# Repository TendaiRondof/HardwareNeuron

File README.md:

# HardwareNeuron
Eine Brufsmaturitätsarbeit für die BBW Winterthur.

## Abstract
### Deutsch
In dieser BMA stellen wir, Tendai und Malik, uns die Frage, ob es möglich ist, mit simplen elektronischen Bauteilen eine Schaltung zu entwerfen, die bestimmte, elementare Logik erlernen und anschliessend wiedergeben kann. Um dies zu erreichen, verwenden wir das Modell eines Neurons. Wir erläutern Struktur und Funktion des biologischen und des informatischen Modells. Schliesslich fällt unsere, ausführlich begründete Entscheidung auf das spiking neural Network. Das die Version des informatischen Modells, welches dem bioligischen am nächsten kommt. Danach nähern wir uns mittels mathematischen Formeln, basierend auf dem spiking neural Network, den Funktionen an, welche die Schaltung erfüllen muss. Darauffolgend werden die Teilfunktionen erklärt und es wird erläutert, wie unsere Schaltung sie bewältigen soll. Die Messungen des Prototypen zeigen, dass die Vorwärtsrechnung, also das wiedergeben des gelernten, funktioniert. Das Problem ist, dass bei unserem Endprodukt nichts funktioniert, da die Leiterbahnen auf dieser Version sehr kurzschlussanfällig sind und wir keine Zeit mehr hatten, alle Kurzschlüsse zu beheben.
### English
In this BMA we, that’s Malik and Tendai, ask ourselves, wether or not it’s possible, to design an electrical circuit, which can learn certain, elementary logic and replicate it subsequently. In order to reach this, we use the model of a neuron. We explain structure and function of the biological and informatical model. In the end, our decision falls onto the spiking neural network. That’s the informatical model, which comes closest to the biological one. Then, we draw up the functions, that our circuit has to implement, through mathematical formulas. After that, the purposes of the smaller subcircuits, we designed, is explained. In the measurements of the Prototype it is shown, that the replication of logic works. Unfortunately the learning itself doesn’t. Besides of that, our final product doesn’t work at all, because there are shortcircuits all over the print and we didn’t have time, to repair them all.

Von Tendai Rondof und Malik Schneider

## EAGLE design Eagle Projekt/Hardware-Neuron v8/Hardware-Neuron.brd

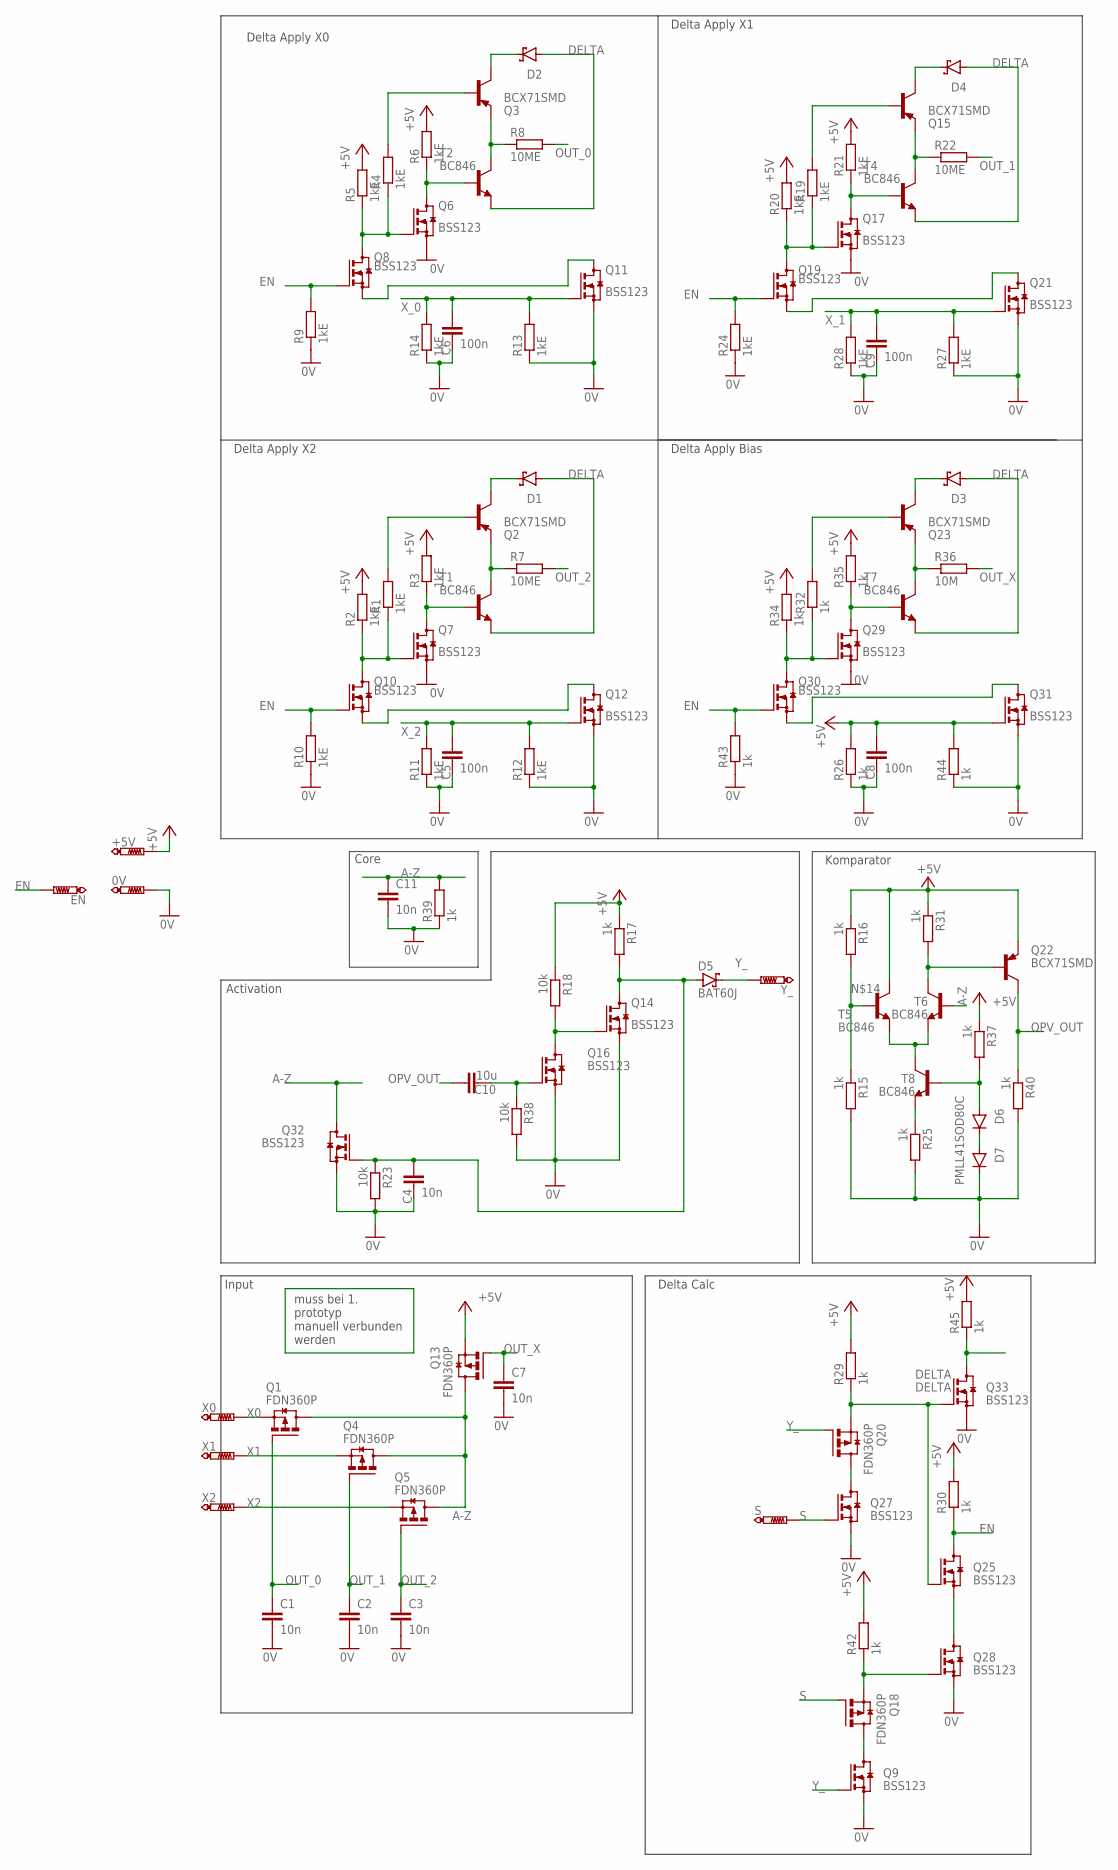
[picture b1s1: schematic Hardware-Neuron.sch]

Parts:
0V: PTR1PAD1-17; P1-17
+5V: PTR1PAD1-17; P1-17
C1, C2, C3, C4, C7, C11: 10n; C0805
C5, C6, C8, C9: 100n; C0805
C10: 10u; C0805
D1, D2, D3, D4, D5: BAT60J; SOD323_ST
D6, D7: PMLL41SOD80C; SOD80C
EN: PTR1PAD1-17; P1-17
Q1, Q4, Q5, Q13, Q18, Q20: FDN360P; SUPER-SOT3
Q2, Q3, Q15, Q22, Q23: BCX71SMD; SOT23
Q6, Q7, Q8, Q9, Q10, Q11, Q12, Q14, Q16, Q17, Q19, Q21, Q25, Q27, Q28, Q29, Q30, Q31, Q32, Q33: BSS123; SOT23
R1, R2, R3, R4, R5, R6, R9, R10, R11, R12, R13, R14, R19, R20, R21, R24, R27, R28: 1kE; M0805
R7, R8, R22: 10ME; M0805
R15, R16, R17, R25, R26, R29, R30, R31, R32, R34, R35, R37, R39, R40, R42, R43, R44, R45: 1k; M0805
R18, R23, R38: 10k; M0805
R36: 10M; M0805
S: PTR1PAD1-17; P1-17
T1, T2, T4, T5, T6, T7, T8: BC846; SOT23
X0, X1, X2: PTR1PAD1-17; P1-17
Y_: PTR1PAD1-17; P1-17

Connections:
0V: 0V.TP, C1.2, C2.2, C3.2, C4.2, C5.2, C6.2, C7.2, C8.2, C9.2, C11.2, D7.C, Q6.2 (S), Q7.2 (S), Q9.2 (S), Q11.2 (S), Q12.2 (S), Q14.2 (S), Q16.2 (S), Q17.2 (S), Q21.2 (S), Q27.2 (S), Q28.2 (S), Q29.2 (S), Q31.2 (S), Q32.2 (S), Q33.2 (S), R9.1, R10.1, R11.1, R12.1, R13.1, R14.1, R15.2, R23.2, R24.1, R25.2, R26.1, R27.1, R28.1, R38.2, R39.1, R40.2, R43.1, R44.1
+5V: +5V.TP, C8.1, Q13.2 (S), Q22.2 (E), Q31.1 (G), R2.2, R3.2, R5.2, R6.2, R16.1, R17.1, R18.1, R20.2, R21.2, R26.2, R29.2, R30.2, R31.1, R34.2, R35.2, R37.1, R42.2, R44.2, R45.2, T5.3 (C)
A-Z: C11.1, Q1.3 (D), Q4.3 (D), Q5.3 (D), Q13.3 (D), Q32.3 (D), R39.2, T6.1 (B)
DELTA: D1.A, D2.A, D3.A, D4.A, Q20.2 (S), Q25.1 (G), Q33.1 (G), R29.1, T1.2 (E), T2.2 (E), T4.2 (E), T7.2 (E)
EN: EN.TP, Q8.1 (G), Q10.1 (G), Q19.1 (G), Q25.3 (D), Q30.1 (G), R9.2, R10.2, R24.2, R30.1, R43.2
unnamed: Q29.3 (D), R35.1, T7.1 (B)
unnamed: Q23.2 (E), R36.1, T7.3 (C)
unnamed: C10.2, Q16.1 (G), R38.1
unnamed: Q33.3 (D), R45.1
unnamed: Q14.1 (G), Q16.3 (D), R18.2
unnamed: Q6.3 (D), R6.1, T2.1 (B)
unnamed: Q8.2 (S), Q11.3 (D)
unnamed: Q3.2 (E), R8.1, T2.3 (C)
unnamed: D3.C, Q23.3 (C)
unnamed: Q23.1 (B), R32.2
unnamed: Q29.1 (G), Q30.3 (D), R32.1, R34.1
unnamed: Q30.2 (S), Q31.3 (D)
unnamed: D6.C, D7.A
unnamed: R15.1, R16.2, T5.1 (B)
unnamed: C4.1, D5.A, Q14.3 (D), Q32.1 (G), R17.2, R23.1
unnamed: Q9.3 (D), Q18.3 (D)
unnamed: R25.1, T8.2 (E)
unnamed: Q22.1 (B), R31.2, T6.3 (C)
unnamed: T5.2 (E), T6.2 (E), T8.3 (C)
unnamed: Q17.3 (D), R21.1, T4.1 (B)
unnamed: D6.A, R37.2, T8.1 (B)
unnamed: D2.C, Q3.3 (C)
unnamed: Q20.3 (D), Q27.3 (D)
unnamed: Q15.2 (E), R22.1, T4.3 (C)
unnamed: Q3.1 (B), R4.2
unnamed: Q6.1 (G), Q8.3 (D), R4.1, R5.1
unnamed: Q18.2 (S), Q28.1 (G), R42.1
unnamed: D4.C, Q15.3 (C)
unnamed: Q15.1 (B), R19.2
unnamed: Q25.2 (S), Q28.3 (D)
unnamed: Q17.1 (G), Q19.3 (D), R19.1, R20.1
unnamed: Q19.2 (S), Q21.3 (D)
unnamed: Q7.3 (D), R3.1, T1.1 (B)
unnamed: Q2.2 (E), R7.1, T1.3 (C)
unnamed: D1.C, Q2.3 (C)
unnamed: Q2.1 (B), R1.2
unnamed: Q7.1 (G), Q10.3 (D), R1.1, R2.1
unnamed: Q10.2 (S), Q12.3 (D)
OPV_OUT: C10.1, Q22.3 (C), R40.1
OUT_0: C1.1, Q1.1 (G), R8.2
OUT_1: C2.1, Q4.1 (G), R22.2
OUT_2: C3.1, Q5.1 (G), R7.2
OUT_X: C7.1, Q13.1 (G), R36.2
S: Q18.1 (G), Q27.1 (G), S.TP
X0: Q1.2 (S), X0.TP
X1: Q4.2 (S), X1.TP
X2: Q5.2 (S), X2.TP
X_0: C6.1, Q11.1 (G), R13.2, R14.2
X_1: C9.1, Q21.1 (G), R27.2, R28.2
X_2: C5.1, Q12.1 (G), R11.2, R12.2
Y_: D5.C, Q9.1 (G), Q20.1 (G), Y_.TP

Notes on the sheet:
Activation
Core
Input
Delta Calc
Komparator
Delta Apply X0
Delta Apply X1
Delta Apply X2
Delta Apply Bias
muss bei 1. prototyp manuell verbunden werden

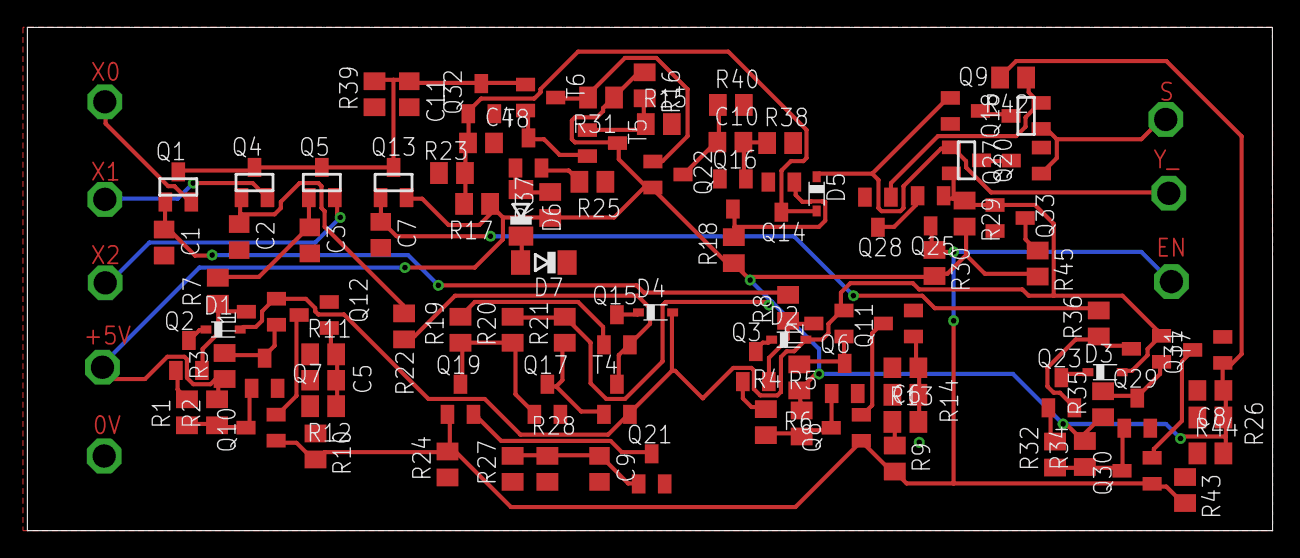
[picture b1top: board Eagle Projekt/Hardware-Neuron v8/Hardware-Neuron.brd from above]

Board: 2 copper layers, 91.0 x 36.8 mm, 107 parts (0 on the bottom side), 56 nets.

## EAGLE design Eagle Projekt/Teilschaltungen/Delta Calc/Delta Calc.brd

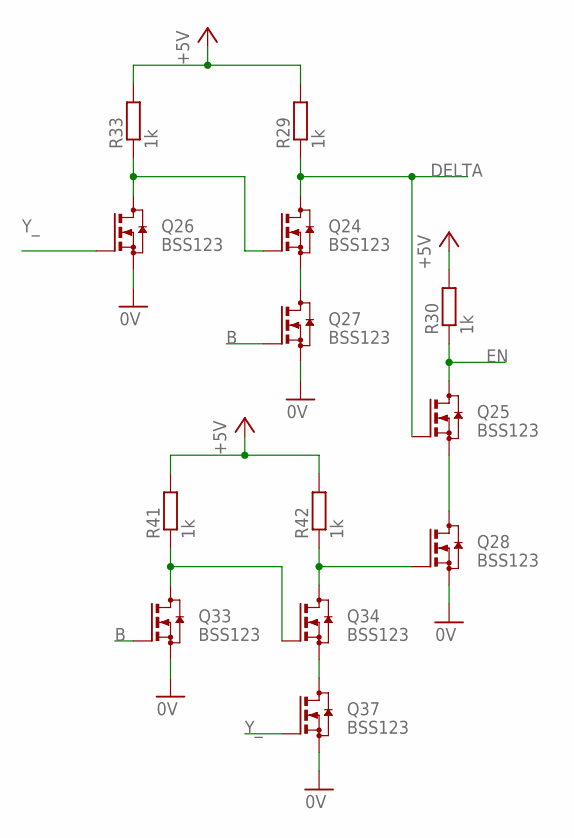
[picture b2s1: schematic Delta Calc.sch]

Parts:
Q24, Q25, Q26, Q27, Q28, Q33, Q34, Q37: BSS123; SOT23
R29, R30, R33, R41, R42: 1k; M0805

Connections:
0V: Q26.2 (S), Q27.2 (S), Q28.2 (S), Q33.2 (S), Q37.2 (S)
+5V: R29.2, R30.2, R33.2, R41.2, R42.2
B: Q27.1 (G), Q33.1 (G)
DELTA: Q24.3 (D), Q25.1 (G), R29.1
EN: Q25.3 (D), R30.1
unnamed: Q24.1 (G), Q26.3 (D), R33.1
unnamed: Q24.2 (S), Q27.3 (D)
unnamed: Q28.1 (G), Q34.3 (D), R42.1
unnamed: Q33.3 (D), Q34.1 (G), R41.1
unnamed: Q25.2 (S), Q28.3 (D)
unnamed: Q34.2 (S), Q37.3 (D)
Y_: Q26.1 (G), Q37.1 (G)

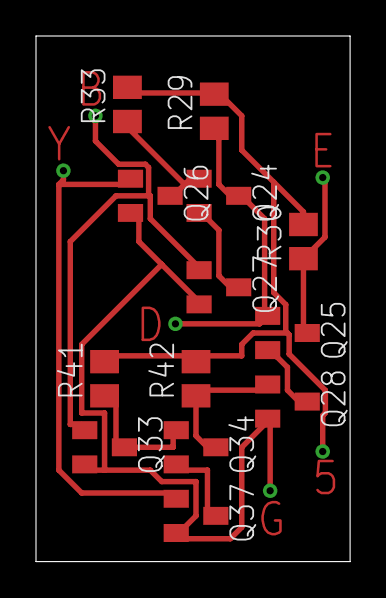
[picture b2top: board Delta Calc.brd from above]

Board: 2 copper layers, 17.4 x 29.2 mm, 13 parts (0 on the bottom side), 12 nets.

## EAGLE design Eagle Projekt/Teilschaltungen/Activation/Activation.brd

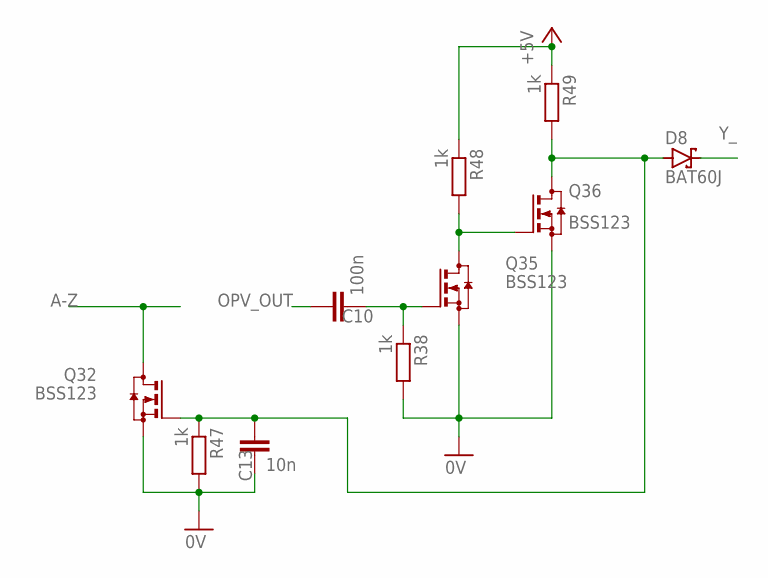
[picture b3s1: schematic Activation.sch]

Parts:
C10: 100n; C0805
C13: 10n; C0805
D8: BAT60J; SOD323_ST
Q32, Q35, Q36: BSS123; SOT23
R38, R47, R48, R49: 1k; M0805

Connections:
0V: C13.2, Q32.2 (S), Q35.2 (S), Q36.2 (S), R38.2, R47.2
+5V: R48.1, R49.1
A-Z: Q32.3 (D)
unnamed: C10.2, Q35.1 (G), R38.1
unnamed: Q35.3 (D), Q36.1 (G), R48.2
unnamed: C13.1, D8.A, Q32.1 (G), Q36.3 (D), R47.1, R49.2
OPV_OUT: C10.1
Y_: D8.C

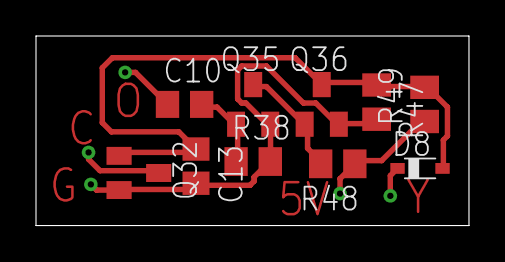
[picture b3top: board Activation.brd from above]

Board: 2 copper layers, 24.1 x 10.5 mm, 10 parts (0 on the bottom side), 5 nets.

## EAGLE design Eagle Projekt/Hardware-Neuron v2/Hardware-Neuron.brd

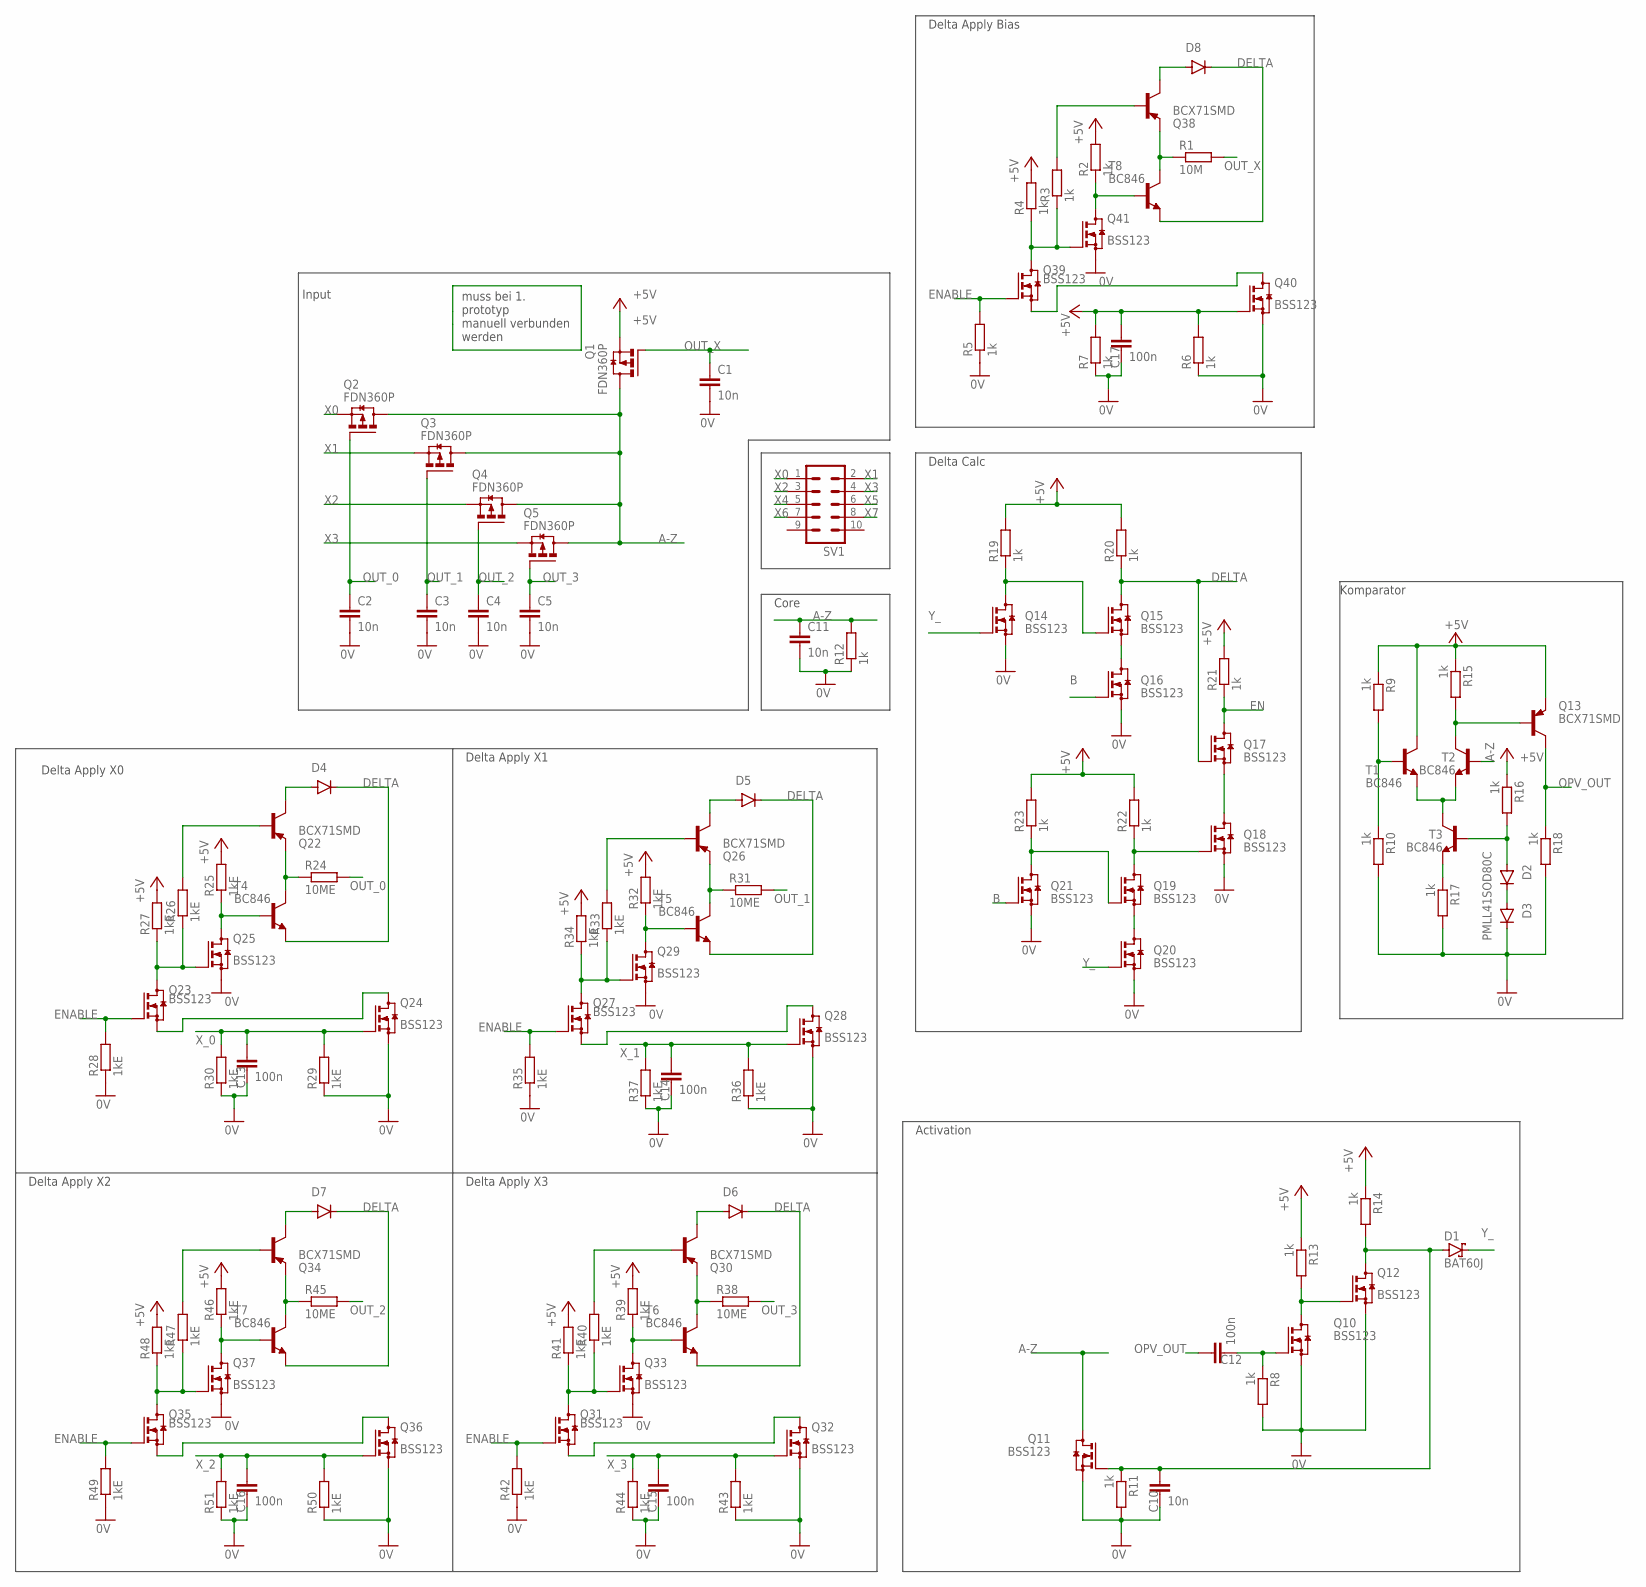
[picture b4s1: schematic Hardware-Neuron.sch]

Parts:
C1, C2, C3, C4, C5, C10, C11: 10n; C1206
C12, C13, C14, C15, C16, C17: 100n; C1206
D1: BAT60J; SOD323_ST
D2, D3, D4, D5, D6, D7, D8: PMLL41SOD80C; SOD80C
Q1, Q2, Q3, Q4, Q5: FDN360P; SUPER-SOT3
Q10, Q11, Q12, Q14, Q15, Q16, Q17, Q18, Q19, Q20, Q21, Q23, Q24, Q25, Q27, Q28, Q29, Q31, Q32, Q33, Q35, Q36, Q37, Q39, Q40, Q41: BSS123; SOT23
Q13, Q22, Q26, Q30, Q34, Q38: BCX71SMD; SOT23
R1: 10M; R1206
R2, R3, R4, R5, R6, R7, R8, R9, R10, R11, R12, R13, R14, R15, R16, R17, R18, R19, R20, R21, R22, R23: 1k; R1206
R24, R31, R38, R45: 10ME; R1206
R25, R26, R27, R28, R29, R30, R32, R33, R34, R35, R36, R37, R39, R40, R41, R42, R43, R44, R46, R47, R48, R49, R50, R51: 1kE; R1206
SV1: ML10
T1, T2, T3, T4, T5, T6, T7, T8: BC846; SOT23

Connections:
0V: C1.2, C2.2, C3.2, C4.2, C5.2, C10.2, C11.2, C13.2, C14.2, C15.2, C16.2, C17.2, D3.C, Q10.2 (S), Q11.2 (S), Q12.2 (S), Q14.2 (S), Q16.2 (S), Q18.2 (S), Q20.2 (S), Q21.2 (S), Q24.2 (S), Q25.2 (S), Q28.2 (S), Q29.2 (S), Q32.2 (S), Q33.2 (S), Q36.2 (S), Q37.2 (S), Q40.2 (S), Q41.2 (S), R5.1, R6.1, R7.1, R8.2, R10.2, R11.2, R12.1, R17.2, R18.2, R28.1, R29.1, R30.1, R35.1, R36.1, R37.1, R42.1, R43.1, R44.1, R49.1, R50.1, R51.1
+5V: C17.1, Q1.2 (S), Q13.2 (E), Q40.1 (G), R2.2, R4.2, R6.2, R7.2, R9.1, R13.1, R14.1, R15.1, R16.1, R19.2, R20.2, R21.2, R22.2, R23.2, R25.2, R27.2, R32.2, R34.2, R39.2, R41.2, R46.2, R48.2, T1.3 (C)
A-Z: C11.1, Q1.3 (D), Q2.3 (D), Q3.3 (D), Q4.3 (D), Q5.3 (D), Q11.3 (D), R12.2, T2.1 (B)
B: Q16.1 (G), Q21.1 (G)
DELTA: D4.C, D5.C, D6.C, D7.C, D8.C, Q15.3 (D), Q17.1 (G), R20.1, T4.2 (E), T5.2 (E), T6.2 (E), T7.2 (E), T8.2 (E)
EN: Q17.3 (D), R21.1
ENABLE: Q23.1 (G), Q27.1 (G), Q31.1 (G), Q35.1 (G), Q39.1 (G), R5.2, R28.2, R35.2, R42.2, R49.2
unnamed: Q41.3 (D), R2.1, T8.1 (B)
unnamed: Q38.2 (E), R1.1, T8.3 (C)
unnamed: C12.2, Q10.1 (G), R8.1
unnamed: C10.1, D1.A, Q11.1 (G), Q12.3 (D), R11.1, R14.2
unnamed: Q10.3 (D), Q12.1 (G), R13.2
unnamed: Q25.3 (D), R25.1, T4.1 (B)
unnamed: Q23.2 (S), Q24.3 (D)
unnamed: Q22.2 (E), R24.1, T4.3 (C)
unnamed: D8.A, Q38.3 (C)
unnamed: Q38.1 (B), R3.2
unnamed: Q39.3 (D), Q41.1 (G), R3.1, R4.1
unnamed: Q39.2 (S), Q40.3 (D)
unnamed: D2.C, D3.A
unnamed: R9.2, R10.1, T1.1 (B)
unnamed: R17.1, T3.2 (E)
unnamed: Q13.1 (B), R15.2, T2.3 (C)
unnamed: T1.2 (E), T2.2 (E), T3.3 (C)
unnamed: Q29.3 (D), R32.1, T5.1 (B)
unnamed: D2.A, R16.2, T3.1 (B)
unnamed: Q14.3 (D), Q15.1 (G), R19.1
unnamed: D4.A, Q22.3 (C)
unnamed: Q15.2 (S), Q16.3 (D)
unnamed: Q26.2 (E), R31.1, T5.3 (C)
unnamed: Q22.1 (B), R26.2
unnamed: Q23.3 (D), Q25.1 (G), R26.1, R27.1
unnamed: Q18.1 (G), Q19.3 (D), R22.1
unnamed: Q19.1 (G), Q21.3 (D), R23.1
unnamed: D5.A, Q26.3 (C)
unnamed: Q26.1 (B), R33.2
unnamed: Q17.2 (S), Q18.3 (D)
unnamed: Q27.3 (D), Q29.1 (G), R33.1, R34.1
unnamed: Q27.2 (S), Q28.3 (D)
unnamed: Q19.2 (S), Q20.3 (D)
unnamed: Q33.3 (D), R39.1, T6.1 (B)
unnamed: Q30.2 (E), R38.1, T6.3 (C)
unnamed: D6.A, Q30.3 (C)
unnamed: Q30.1 (B), R40.2
unnamed: Q31.3 (D), Q33.1 (G), R40.1, R41.1
unnamed: Q31.2 (S), Q32.3 (D)
unnamed: Q37.3 (D), R46.1, T7.1 (B)
unnamed: Q34.2 (E), R45.1, T7.3 (C)
unnamed: D7.A, Q34.3 (C)
unnamed: Q34.1 (B), R47.2
unnamed: Q35.3 (D), Q37.1 (G), R47.1, R48.1
unnamed: Q35.2 (S), Q36.3 (D)
OPV_OUT: C12.1, Q13.3 (C), R18.1
OUT_0: C2.1, Q2.1 (G), R24.2
OUT_1: C3.1, Q3.1 (G), R31.2
OUT_2: C4.1, Q4.1 (G), R45.2
OUT_3: C5.1, Q5.1 (G), R38.2
OUT_X: C1.1, Q1.1 (G), R1.2
X0: Q2.2 (S), SV1.1
X1: Q3.2 (S), SV1.2
X2: Q4.2 (S), SV1.3
X3: Q5.2 (S), SV1.4
X4: SV1.5
X5: SV1.6
X6: SV1.7
X7: SV1.8
X_0: C13.1, Q24.1 (G), R29.2, R30.2
X_1: C14.1, Q28.1 (G), R36.2, R37.2
X_2: C16.1, Q36.1 (G), R50.2, R51.2
X_3: C15.1, Q32.1 (G), R43.2, R44.2
Y_: D1.C, Q14.1 (G), Q20.1 (G)

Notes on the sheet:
Activation
Core
Input
Delta Calc
Komparator
Delta Apply X0
Delta Apply X1
Delta Apply X2
Delta Apply X3
Delta Apply Bias
muss bei 1. prototyp manuell verbunden werden

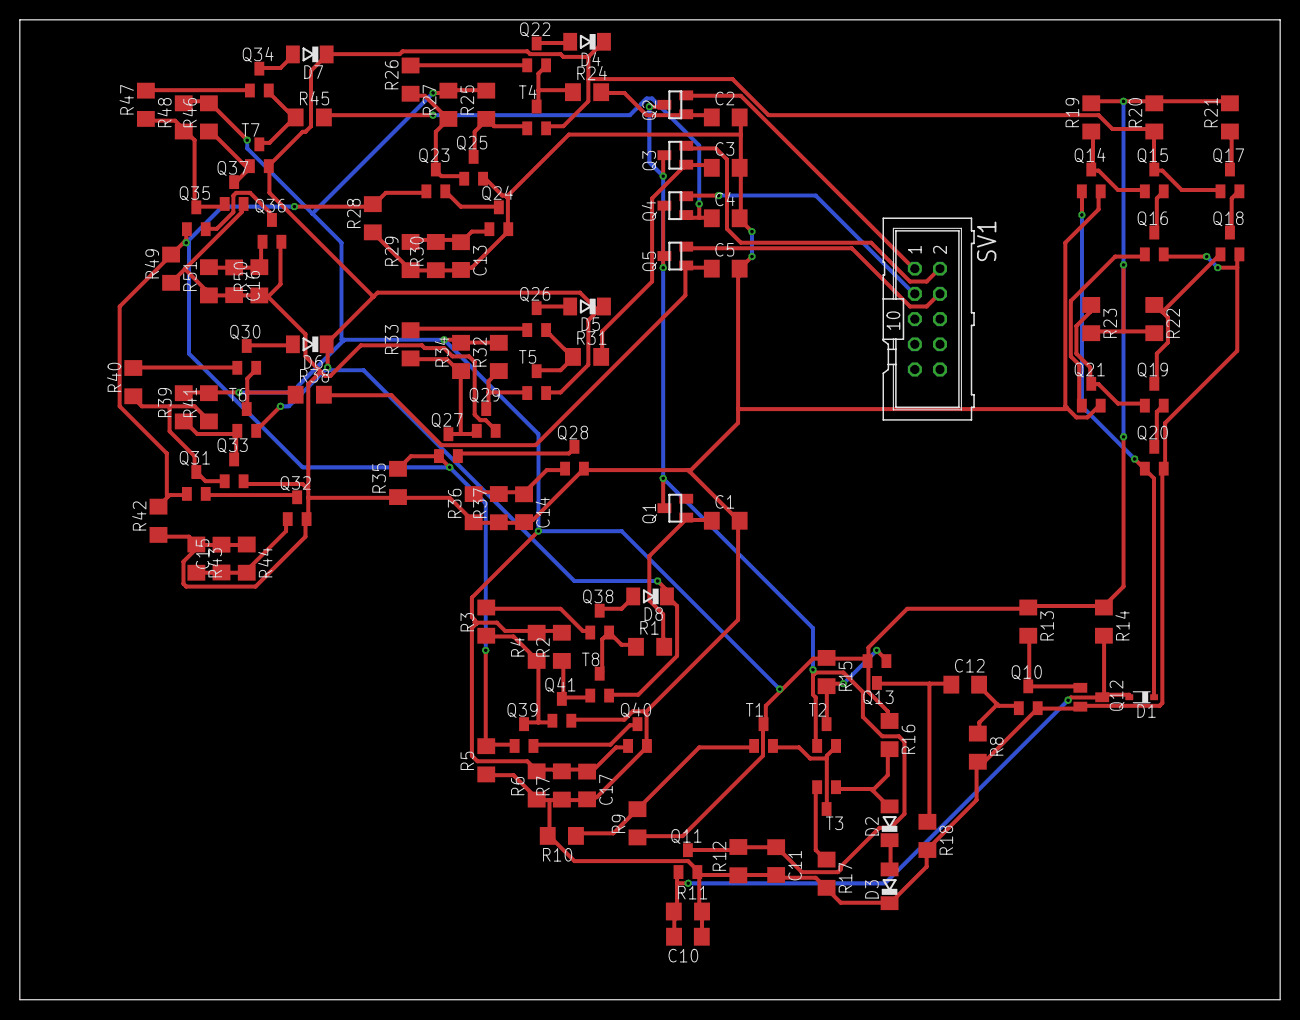
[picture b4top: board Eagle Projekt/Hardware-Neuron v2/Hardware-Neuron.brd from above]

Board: 2 copper layers, 127.0 x 98.7 mm, 118 parts (0 on the bottom side), 67 nets.

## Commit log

2019-11-02 First Push
    Project Staring up
2019-11-02 Moved File
2019-11-02 moved files
2019-11-02 updated v2
2019-11-02 changed v2
2019-11-02 Multisim V2 updated
    Erstes volles update von den Multisim Dateien
2019-11-09 titelblatt + layout
2019-11-18 added AARs
2019-11-18 AAR 3 erstellt
2019-11-18 Multisim HardwareNeuronV3
    Activation and Delta Apply have been updated
2019-11-23 malik aar und eagle
2019-11-23 überarbeitet
2019-11-24 layout angepasst
2019-11-25 Eagle Korrektur
    (Nur oberflächlich)
2019-11-30 Cosmetics
    Eagle Kontrolliert, Dokumente geortnet
2019-11-30 fixed
2019-11-30 vorwort
2019-12-01 gschribe
2019-12-01 Dokufiles
2019-12-01 Grammatikalische Korrektur
2019-12-01 Mathematisches Model
2019-12-01 schreiben
2019-12-03 Doku Berechnung
2019-12-03 update againXD
2019-12-14 dimensionierung
2019-12-14 verschönerung in v3
2019-12-28 Version 4
    Neue Version hinzugefügt
2020-01-05 Update von V4
    Schwierig
2020-01-07 aar 4
2020-01-09 stückliste
2020-01-09 Layout upgrade
2020-01-10 anpassung stkliste
2020-01-13 Komentar Update
2020-01-17 programming
2020-01-18 layout
2020-01-18 senf
2020-01-18 tendai hinzuegfüegt
2020-01-18 tralala
2020-01-18 änderungen
2020-01-19 zügs
2020-01-21 Anpassung der Dokumentation
2020-01-22 stückliste und so
2020-02-02 Verschönerung des Kommentars
2020-02-03 abstract
2020-02-03 Changes?
2020-02-16 presi
